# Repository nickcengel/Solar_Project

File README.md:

# Solar_Project
MPPT solar battery charger with sun tracking and wifi

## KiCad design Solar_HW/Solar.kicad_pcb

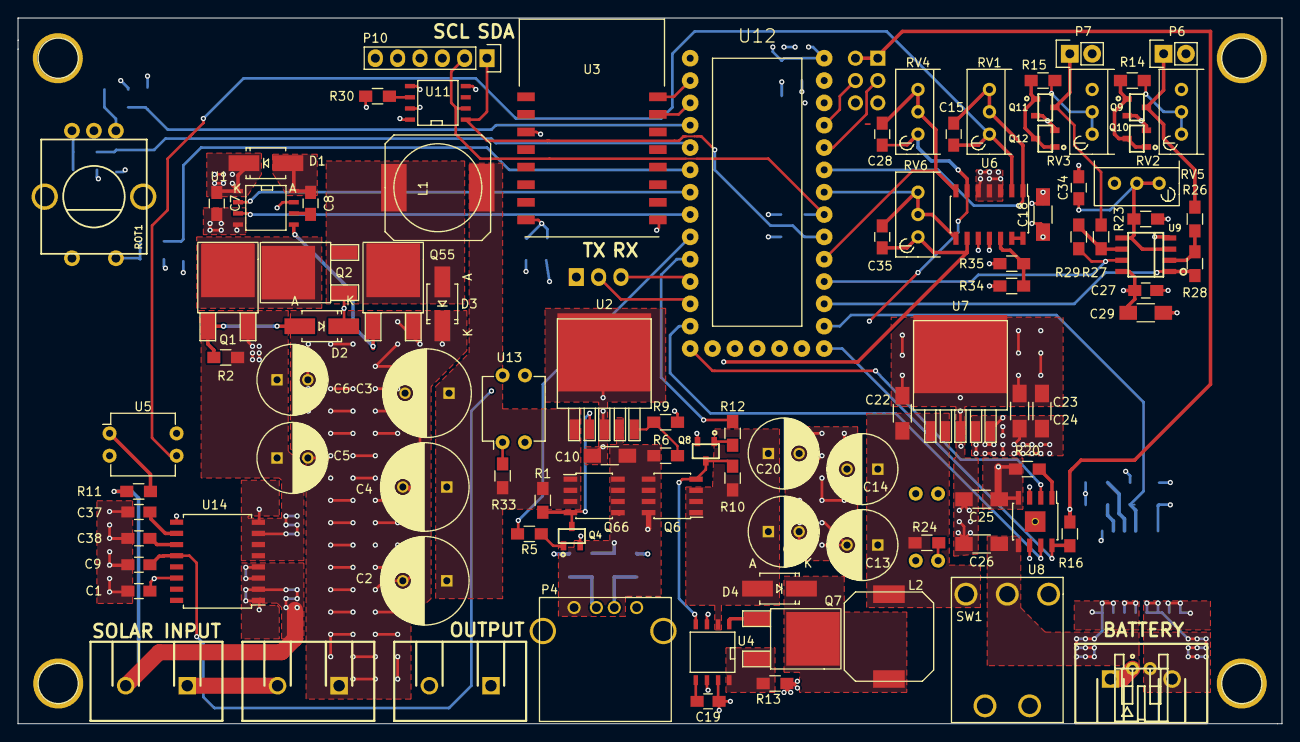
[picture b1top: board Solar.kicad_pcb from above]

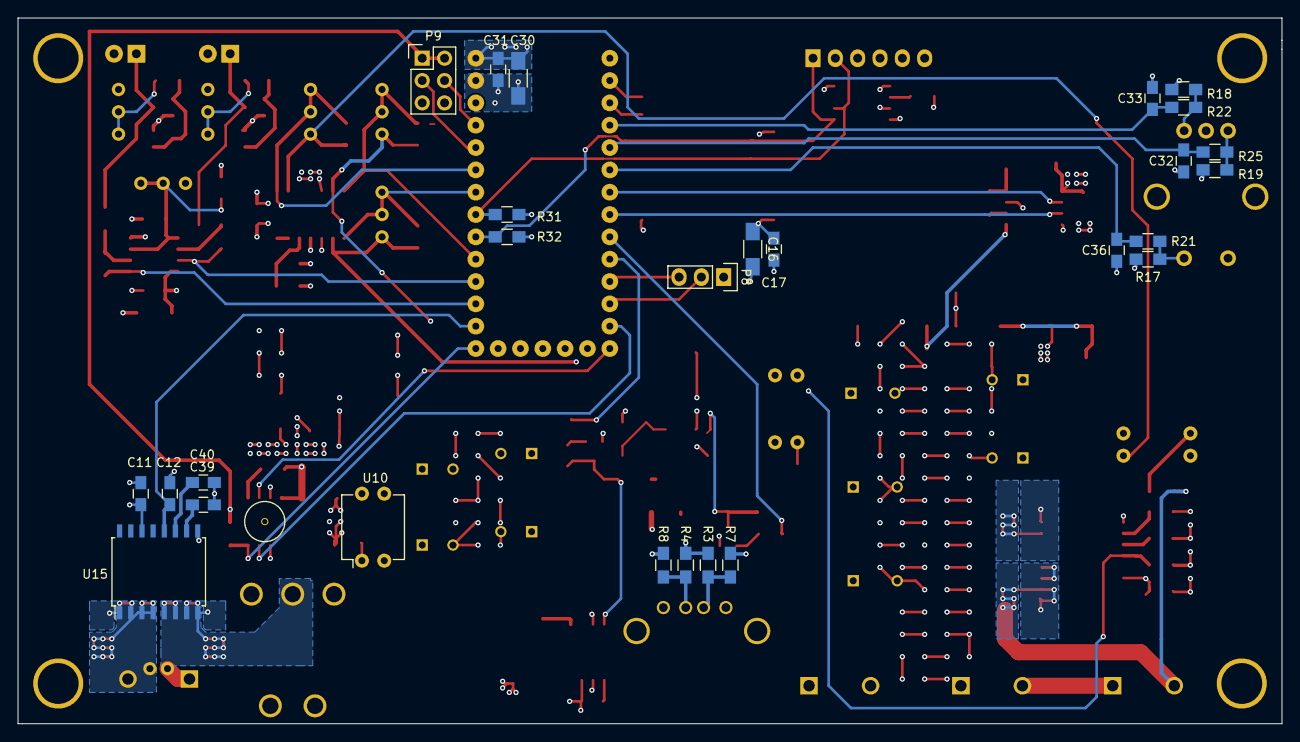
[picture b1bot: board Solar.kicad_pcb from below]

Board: 4 copper layers, 143.8 x 80.3 mm, 127 parts (27 on the bottom side), 80 nets.

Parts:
C1, C7, C8, C9, C11, C12, C17, C19, C27, C31, C37, C38, C39, C40: .1u; C_0805_HandSoldering
C2, C3, C4: 1000u; C_Radial_D10_L16_P5
C5, C6, C13, C14, C20, C21: 220U; C_Radial_D8_L11.5_P3.5
C10, C16, C18, C22, C23, C24, C25, C26, C29, C30: 22U; C_1206_HandSoldering
C15, C28, C32, C33, C35, C36: .01u; C_0805_HandSoldering
C34: 1u; C_0805_HandSoldering
D1, D2, D3, D4: MBRA340T3G; Diode-SMA_Handsoldering
JST-S2B-PH-K_right-angle-jack: VAL**; JST-S2B-PH-K_right-angle-jack
L1: 330uH; SELF-WE-PD-XXL
L2: 22U; self_cms_we-tpc_XL
P1, P2, P3, P5: CONN_01X02; 1x2-SCREW-TERM_P7.5mm
P4: USB_A
P6, P7: CONN_01X02; Pin_Header_Straight_1x02
P8: CONN_01X03; Pin_Header_Straight_1x03
P9: CONN_02X03; Pin_Header_Straight_2x03
P10: CONN_01X06; Pin_Header_Straight_1x06
Q1, Q2, Q7, Q55: IRF3704Z; DPAK-2
Q4, Q8: PN2222A; SOT23
Q6, Q66: FDS4465; SOIC-8_3.9x4.9mm_Pitch1.27mm
Q9, Q10, Q11, Q12: PNP_BEC; SOT23
R1, R10: 330k; R_0805_HandSoldering
R2, R11, R16, R17, R18, R19, R20, R21, R22, R25, R30, R34, R35: 10k; R_0805_HandSoldering
R3: 42.9k; R_0805_HandSoldering
R4: 74.4k; R_0805_HandSoldering
R5, R12: 1k; R_0805_HandSoldering
R6: 180k; R_0805_HandSoldering
R7, R8: 49.3k; R_0805_HandSoldering
R9: 16k; R_0805_HandSoldering
R13: 50m; R_0805_HandSoldering
R14, R15: 2.2k; R_0805_HandSoldering
R23, R24: 2.7k; R_0805_HandSoldering
R26, R27: 12k; R_0805_HandSoldering
R28, R29: 47k; R_0805_HandSoldering
R31, R32: 4.7k; R_0805_HandSoldering
R33: 3.3k; R_0805_HandSoldering
ROT1: ROTARY-ENCODER; SF-ROTARY-ENCODER
RV1, RV4, RV6: POT; Potentiometer_Bourns_3296W_3-8Zoll_Inline_ScrewUp
RV2, RV3, RV5: 1k; Potentiometer_Bourns_3296W_3-8Zoll_Inline_ScrewUp
SW1: SW_SPDT; SPDT_Toggle
U1: IR2104; SOIC-8-N
U2: MCP1827; DPAK-5
U3: ESP8266; ESP8266_ADAFRUIT_SMD
U4: MAX770; SOIC-8-N
U5, U10, U13: LTV-817; DIP-4_W7.62mm
U6: LMV324; SOIC-14_3.9x8.7mm_Pitch1.27mm
U7: LT1963; DPAK-5
U8: MAX1811; SOIC-8-1EP_3.9x4.9mm_Pitch1.27mm
U9: TL072; SOIC8
U11: DS75; SOIC-8-N
U12: Teensy_3.1
U14, U15: ACS710; SOIC-16_7.5x10.3mm_Pitch1.27mm

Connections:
5V_OUT: C10.1, C25.1, P1.1, P4.1, P9.1, P9.2, Q6.5, Q6.6, Q6.7, Q6.8, Q66.5, Q66.6, Q66.7, Q66.8, R3.1, R4.1, R6.1, R16.1, R20.1, U2.4, U8.4
+3V3: C1.1, C11.1, C16.1, C17.1, C18.1, C23.1, C24.1, C27.1, C29.1, C30.1, C31.1, P10.6, Q9.2, Q10.2, Q11.2, Q12.2, R17.1, R18.1, R19.1, R23.1, R30.1, R31.1, R32.1, R34.1, U3.3, U3.8, U6.11, U7.4, U7.5, U9.8, U11.8, U12.26, U14.14, U15.14
BATTERY_I: C12.1, U12.14, U15.12
BATTERY_INPUT: C13.1, C14.1, C22.1, L2.1, R24.1, SW1.2, U7.1, U7.2
BATTERY_INPUT_BUF: C28.2, RV4.2, RV4.3, U6.7, U12.17
CHRG: R16.2, U8.8, U12.13
CHRG_EN: U8.7, U12.11
CHRG_I: U8.2, U12.12
ESP_RX: U3.15, U12.1
ESP_TX: U3.16, U12.0
GND: C1.2, C2.2, C3.2, C4.2, C5.2, C6.2, C7.2, C9.2, C10.2, C11.2, C12.2, C13.2, C14.2, C16.2, C17.2, C18.2, C19.2, C20.2, C21.2, C22.2, C23.2, C24.2, C25.2, C26.2, C27.2, C29.2, C30.2, C31.2, C32.2, C33.2, C34.2, C36.2, C37.2, C38.2, C39.2, C40.2, D3.1, JST-S2B-PH-K_right-angle-jack.1, P1.2, P3.1, P4.4, P4.5, P5.1, P6.2, P7.2, P8.1, P9.5, P9.6, P10.4, Q4.2, Q8.2, Q55.3, R7.2, R8.2, R9.2, R13.2, R35.2, ROT1.3, ROT1.5, RV2.3, RV3.3, RV5.3, U1.4, U2.3, U3.9, U4.3, U4.6, U4.7, U5.2, U5.4, U6.3, U6.4, U6.5, U6.10, U7.3, U8.3, U8.6, U9.4, U10.2, U10.4, U11.4, U11.5, U11.7, U12.25, U12.27, U12.30, U13.2, U13.4, U14.9, U15.9
LIGHT1: R28.2, U9.1, U12.15
LIGHT2: R29.1, U9.7, U12.16
LOAD_SWITCH: R12.1, U12.8
MPPT_PWM: U1.2, U12.5
unnamed: C5.1, C6.1, C7.1, D1.1, Q1.3, R2.1, U1.1, U14.5, U14.6, U14.7, U14.8
unnamed: C8.1, D1.2, U1.8
unnamed: C8.2, U1.6
unnamed: C15.1, RV1.1, U5.3, U6.2
unnamed: C19.1, U4.5
unnamed: C20.1, C21.1, D4.2, Q6.1, Q6.2, Q6.3, R10.2, U4.2
unnamed: C26.1, SW1.1, U8.5, U15.5, U15.6, U15.7, U15.8
unnamed: C28.1, RV4.1, U6.6, U10.3
unnamed: C34.1, R23.2, RV5.1, RV5.2, U9.3, U9.5
unnamed: C35.1, RV6.1, U6.9, U13.3
unnamed: C37.1, U14.10
unnamed: C38.1, U14.11
unnamed: C39.1, U15.10
unnamed: C40.1, U15.11
unnamed: D2.1, Q2.1, U1.7
unnamed: D2.2, Q1.1, R2.2
unnamed: D3.2, L1.1, Q2.3, Q55.2
unnamed: D4.1, L2.2, Q7.2
unnamed: P2.1, P3.2
unnamed: P4.2, R3.2, R7.1
unnamed: P4.3, R4.2, R8.1
unnamed: JST-S2B-PH-K_right-angle-jack.2, P5.2, U15.1, U15.2, U15.3, U15.4
unnamed: P6.1, Q10.3, R26.1
unnamed: P7.1, Q11.3, R27.1
unnamed: Q1.2, Q2.2
unnamed: Q4.1, R5.1
unnamed: Q4.3, Q66.4, R1.2, U2.2
unnamed: Q6.4, Q8.3, R10.1, U4.4
unnamed: Q7.1, U4.1
unnamed: Q7.3, R13.1, U4.8
unnamed: Q8.1, R12.2
unnamed: Q9.1, Q9.3, Q10.1, R14.1
unnamed: Q11.1, Q12.1, Q12.3, R15.1
unnamed: Q55.1, U1.5
unnamed: R6.2, R9.1, U2.5
unnamed: R11.2, U5.1
unnamed: R14.2, RV2.1, RV2.2
unnamed: R15.2, RV3.1, RV3.2
unnamed: R17.2, R21.2, ROT1.1
unnamed: R18.2, R22.2, ROT1.2
unnamed: R19.2, R25.2, ROT1.4
unnamed: R20.2, U8.1
unnamed: R24.2, U10.1
unnamed: R26.2, R28.1, U9.2
unnamed: R27.2, R29.2, U9.6
unnamed: R30.2, U11.6
unnamed: R33.2, U13.1
unnamed: R34.2, R35.1, U6.12
unnamed: U6.13, U6.14
PRE_REG_V: C2.1, C3.1, C4.1, L1.2, Q66.1, Q66.2, Q66.3, R1.1, R33.1, U2.1
PRE_REG_V_BUF: C35.2, RV6.2, RV6.3, U6.8, U12.20
REGULATE: R5.2, U12.7
ROTARY_A: C33.1, R22.1, U12.2
ROTARY_B: C32.1, R25.1, U12.3
ROTARY_BUTTON: C36.1, R21.1, U12.4
RXD: P8.2, U12.10
SCL: P10.2, R31.2, U11.2, U12.19
SDA: P10.1, R32.2, U11.1, U12.18
SERVO1: P9.3, U12.22
SERVO2: P9.4, U12.23
SOLAR_I: C9.1, U12.28, U14.12
SOLAR_INPUT: P2.2, R11.1, U14.1, U14.2, U14.3, U14.4
SOLAR_INPUT_BUF: C15.2, RV1.2, RV1.3, U6.1, U12.21
SOLAR_SHDN: U1.3, U12.6
TXD: P8.3, U12.9

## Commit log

2015-08-01 Create README.md
    created readme document
2015-08-01 Added Info
2015-08-01 Added kicad_pcb-bak
2015-08-01 Added existing schematic/PCB and Gerbers
2015-08-01 test
2015-08-01 Update README.md
    removed info
2015-08-03 final board tweaks, new BOM, Final Gerber sent to SEED
2015-08-03 Deleted old gerbers
2015-08-12 added gcode
